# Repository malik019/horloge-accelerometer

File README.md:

# Ultra-Low-Power ATtiny Motion Clock (Horloge)

A compact, low-power embedded hardware platform featuring an **Microchip ATtiny MCU** integrated with an **STMicroelectronics LIS2DW12 ultra-low-power accelerometer** and **WS2812B-MINI addressable RGB LEDs**. 

This repository houses the complete hardware development lifecycle, from schematic capture and board layout to manufacturing documentation.

## 🛠️ Hardware Specifications & Component Selection
* **Microcontroller:** Microchip ATtiny MCU (optimized for compact footprint and low static power draw).
* **Motion Sensing:** STMicroelectronics LIS2DW12 3-axis accelerometer (selected for its sub-microamp low-power modes and configurable wake-on-motion interrupts).
* **Display / Visuals:** WS2812B-MINI addressable RGB LEDs for custom illumination, animations, or gesture-based feedback.
* **Power Management:** Integrated battery layout interface (CR2032 or similar lithium coin cell support).

## 📂 Repository Architecture
The workspace is organized following standard hardware engineering practices:
* **`/design`** — Primary KiCad project assets containing schematics (`.kicad_sch`), PCB layouts (`.kicad_pcb`), global footprint tables, and specialized local hardware libraries.
* **`/fabrication`** — Production-ready Gerber files, drill plots, and Open Parts List (OPL) Bill of Materials data ready for manufacturing.
* **`/documentation`** — Comprehensive hardware design review documents and exportable schematics in PDF format for immediate evaluation.

## 🚀 Key Engineering Focus Areas
* **Power Optimization:** Leveraged the LIS2DW12 accelerometer's hardware interrupt pins to wake the ATtiny MCU from deep sleep modes, maximizing overall battery runtime.
* **Signal Integrity:** Carefully routed digital signals for the high-speed data lines driving the addressable NeoPixel array while isolating noise near the sensor.
* **Form Factor Constraint:** Designed a dense, highly integrated multi-layer layout tailored for a compact, wearable or portable desk-clock configuration.

## ⚙️ Tools Used
* **EDA Tool:** KiCad (Schematic Capture, PCB Layout, and 3D Visualizer Integration)

## 📺 Demo Video
Click the image below to watch the hardware platform and interface in action:

*[Click here to watch the full project demonstration if the badge above doesn't open.](https://1drv.ms/v/c/b2abd14c679eea6b/IQBb18cBuQbQQaUBIMpuPMWnAfBBgvG3fzTZn4pLQCEiL4w?e=841tbs)*

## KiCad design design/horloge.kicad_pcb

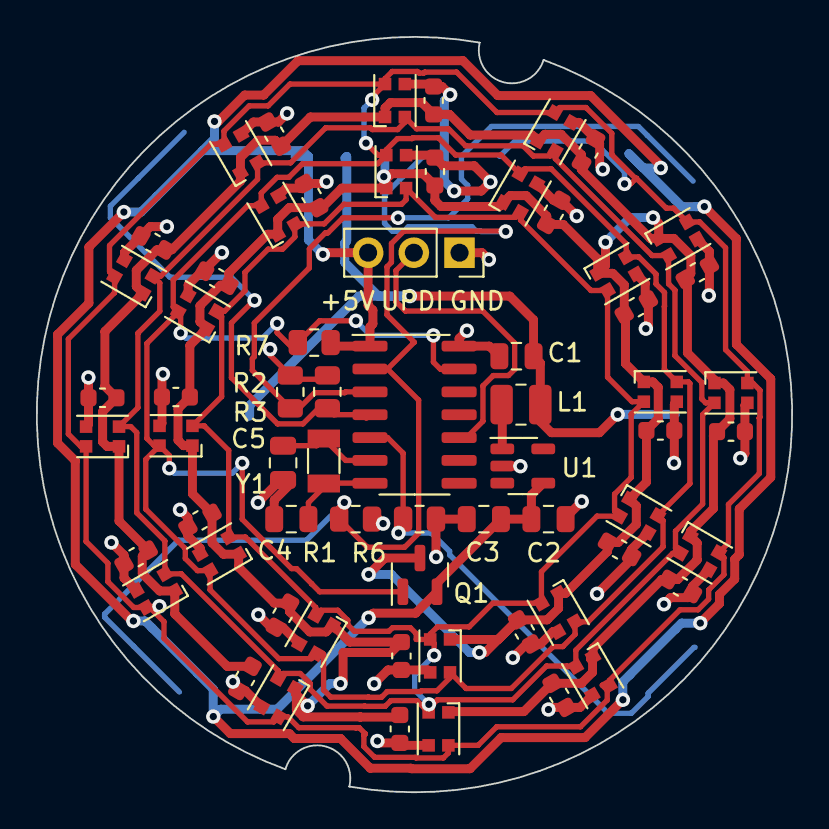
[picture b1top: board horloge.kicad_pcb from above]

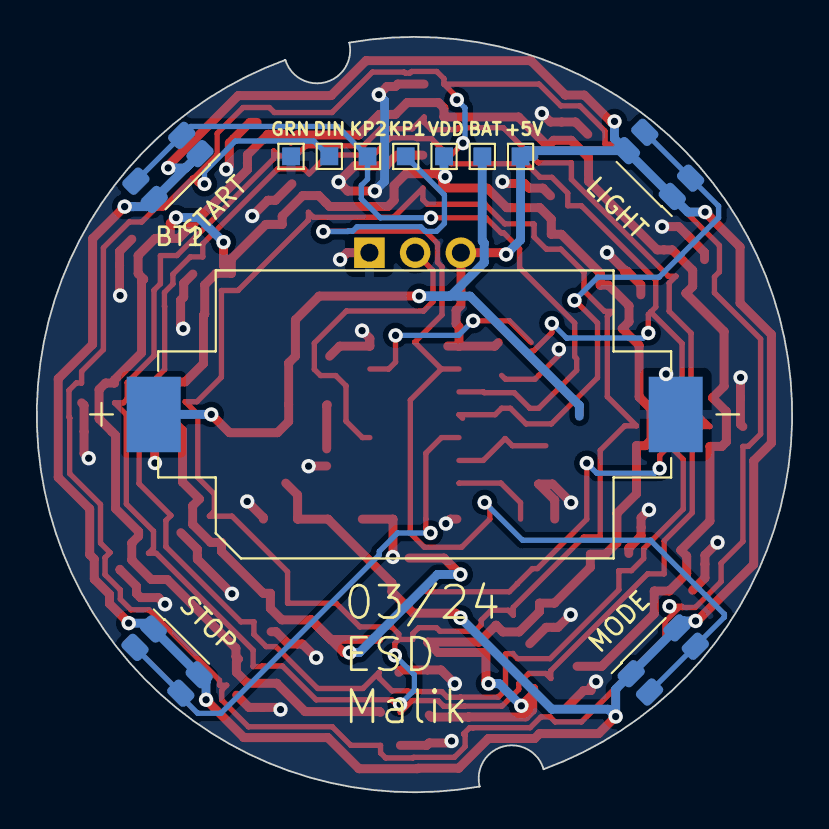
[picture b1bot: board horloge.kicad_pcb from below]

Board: 2 copper layers, 42.0 x 42.0 mm, 76 parts (12 on the bottom side), 14 nets.

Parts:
BT1: Battery_Cell; BAT_CR2032-BS-6-1
C1: 2.2uF; C_0805_2012Metric
C2: 22uF; C_0805_2012Metric
C3: 100nF; C_0805_2012Metric
C4, C5: 12.5pF; C_0805_2012Metric
C9, C10, C11, C12, C13, C14, C15, C16, C17, C18, C19, C20, C21, C22, C23, C24, C25, C26, C27, C28, C29, C30, C31, C32: 100nF; C_0603_1608Metric
D1, D2, D3, D4, D5, D6, D7, D8, D9, D10, D11, D12, D13, D14, D15, D16, D17, D18, D19, D20, D21, D22, D23, D24: WS2812B; LED_WS2812B-2020_PLCC4_2.0x2.0mm
J1, J2, J3, J4, J5, J6, J7: Conn_01x01; TestPoint_Pad_1.0x1.0mm
L1: 4.7uH; L_1008_2520Metric
Q1: Si2319CDS; SOT-23
R1, R2, R3, R6: 10k; R_0805_2012Metric
R7: 100; R_0805_2012Metric
SW1, SW2, SW3, SW4: SW_Push; SW_SPST_EVQP7A
U1: TPS613222ADBV; SOT-23-5
U3: ATtiny814-SS; SOIC-14_3.9x8.7mm_P1.27mm
Y1: 32KHz; Crystal_SMD_3215-2Pin_3.2x1.5mm
upload_point1: Conn_01x03_Pin; PinSocket_1x03_P2.54mm_Vertical

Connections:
+5V: C2.1, C3.2, J1.1, Q1.2 (S), R7.2, SW1.1, SW2.1, SW3.1, SW4.1, U1.4 (VOUT), U3.1 (VCC), upload_point1.3
+BATT: BT1.P, C1.1, J2.1, L1.1
/DIN: D1.4 (DIN), D2.4 (DIN), D3.4 (DIN), D4.4 (DIN), D5.4 (DIN), D6.4 (DIN), D7.4 (DIN), D8.4 (DIN), D9.4 (DIN), D10.4 (DIN), D11.4 (DIN), D12.4 (DIN), D13.4 (DIN), D14.4 (DIN), D15.4 (DIN), D16.4 (DIN), D17.4 (DIN), D18.4 (DIN), D19.4 (DIN), D20.4 (DIN), D21.4 (DIN), D22.4 (DIN), D23.4 (DIN), D24.4 (DIN), J4.1, Q1.1 (G), R7.1, U3.13 (PA3)
/KNOP_1: J5.1, R1.1, SW1.2, U3.2 (PA4)
/KNOP_2: J6.1, R2.1, SW2.2, U3.3 (PA5)
/KNOP_3: R3.1, SW3.2, U3.4 (PA6)
/KNOP_4: R6.1, SW4.2, U3.5 (PA7)
/TOSCS1: C4.2, U3.7 (PB2), Y1.2
/TOSCS2: C5.2, U3.6 (PB3), Y1.1
/UPDI: U3.10 (~RESET/PA0), upload_point1.2
GND: BT1.N, C1.2, C2.2, C3.1, C4.1, C5.1, C9.2, C10.2, C11.2, C12.2, C13.2, C14.2, C15.2, C16.2, C17.2, C18.2, C19.2, C20.2, C21.2, C22.2, C23.2, C24.2, C25.2, C26.2, C27.2, C28.2, C29.2, C30.2, C31.2, C32.2, D1.3 (VSS), D2.3 (VSS), D3.3 (VSS), D4.3 (VSS), D5.3 (VSS), D6.3 (VSS), D7.3 (VSS), D8.3 (VSS), D9.3 (VSS), D10.3 (VSS), D11.3 (VSS), D12.3 (VSS), D13.3 (VSS), D14.3 (VSS), D15.3 (VSS), D16.3 (VSS), D17.3 (VSS), D18.3 (VSS), D19.3 (VSS), D20.3 (VSS), D21.3 (VSS), D22.3 (VSS), D23.3 (VSS), D24.3 (VSS), J7.1, R1.2, R2.2, R3.2, R6.2, U1.2 (GND), U3.14 (GND), upload_point1.1
unnamed: D1.2 (DOUT), D2.2 (DOUT), D3.2 (DOUT), D4.2 (DOUT), D5.2 (DOUT), D6.2 (DOUT), D7.2 (DOUT), D8.2 (DOUT), D9.2 (DOUT), D10.2 (DOUT), D11.2 (DOUT), D12.2 (DOUT), D13.2 (DOUT), D14.2 (DOUT), D15.2 (DOUT), D16.2 (DOUT), D17.2 (DOUT), D18.2 (DOUT), D19.2 (DOUT), D20.2 (DOUT), D21.2 (DOUT), D22.2 (DOUT), D23.2 (DOUT), D24.2 (DOUT)
unnamed: L1.2, U1.1 (SW)
VDD: C9.1, C10.1, C11.1, C12.1, C13.1, C14.1, C15.1, C16.1, C17.1, C18.1, C19.1, C20.1, C21.1, C22.1, C23.1, C24.1, C25.1, C26.1, C27.1, C28.1, C29.1, C30.1, C31.1, C32.1, D1.1 (VDD), D2.1 (VDD), D3.1 (VDD), D4.1 (VDD), D5.1 (VDD), D6.1 (VDD), D7.1 (VDD), D8.1 (VDD), D9.1 (VDD), D10.1 (VDD), D11.1 (VDD), D12.1 (VDD), D13.1 (VDD), D14.1 (VDD), D15.1 (VDD), D16.1 (VDD), D17.1 (VDD), D18.1 (VDD), D19.1 (VDD), D20.1 (VDD), D21.1 (VDD), D22.1 (VDD), D23.1 (VDD), D24.1 (VDD), J3.1, Q1.3 (D)
